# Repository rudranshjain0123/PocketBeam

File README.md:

# PocketBeam

A flashlight right?
Is a flashlight, but a different one. 3 leds, a buzzer and even a darkness detector!

Exactly what we need for those nights when the power cuts.

A MANUAL CONTROL for when u need to have fun.
Powered by 2 aa, this packs a punch.
This is custom made by me in kicad.
# Whats INSIDE
It includes resistors, a capacitator, a detector, switches etc.
### IMG

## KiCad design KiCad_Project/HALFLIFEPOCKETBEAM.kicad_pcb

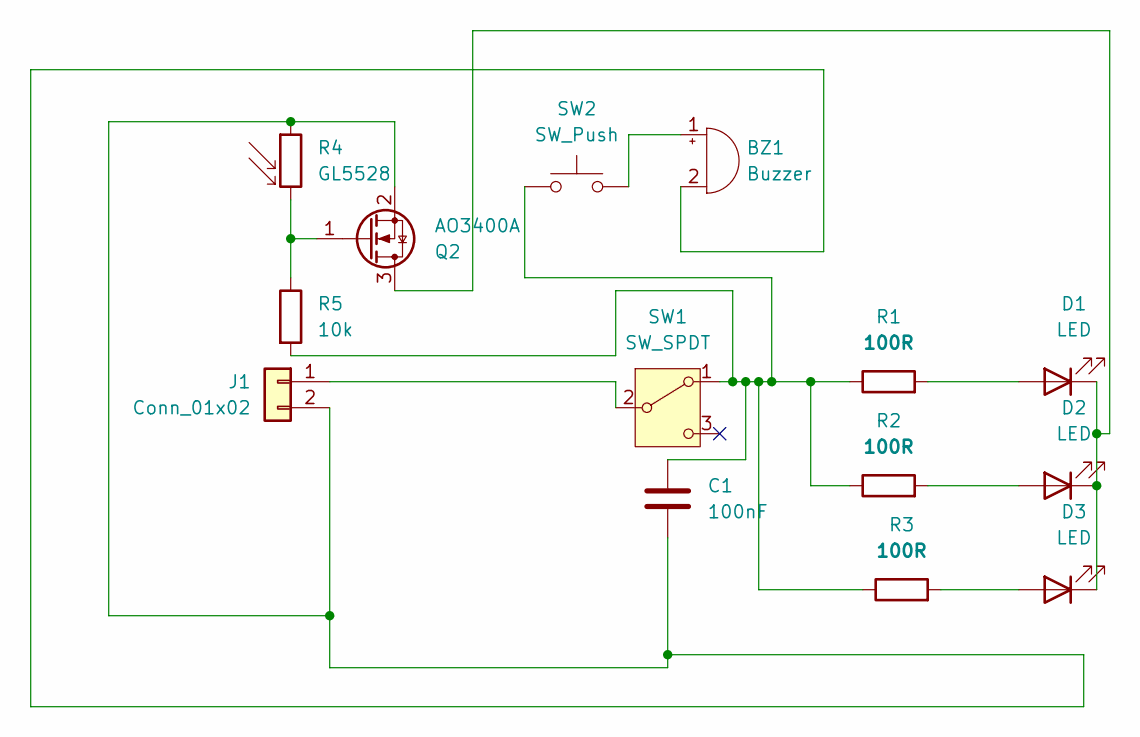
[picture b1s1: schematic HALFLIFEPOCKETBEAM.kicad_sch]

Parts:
BZ1: Buzzer; Buzzer_12x9.5RM7.6
C1: 100nF; C_Disc_D5.0mm_W2.5mm_P5.00mm
D1, D2, D3: LED; LED_D5.0mm_Horizontal_O1.27mm_Z15.0mm
J1: Conn_01x02; PinHeader_1x02_P2.54mm_Vertical
Q2: AO3400A; SOT-23
R1, R2, R3: 100R; R_Axial_DIN0207_L6.3mm_D2.5mm_P10.16mm_Horizontal
R4: GL5528; R_LDR_5.0x4.1mm_P3mm_Vertical
R5: 10k; R_Axial_DIN0207_L6.3mm_D2.5mm_P10.16mm_Horizontal
SW1: SW_SPDT; SW_Slide_SPDT_Straight_CK_OS102011MS2Q
SW2: SW_Push; SW_PUSH_6mm_H13mm

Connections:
unnamed: BZ1.1 (+), SW2.2
unnamed: BZ1.2 (-), C1.2, J1.2, Q2.2 (S), R4.1
unnamed: D1.2 (A), R1.2
unnamed: D1.1 (K), D2.1 (K), D3.1 (K), Q2.3 (D)
unnamed: D2.2 (A), R2.2
unnamed: D3.2 (A), R3.2
unnamed: J1.1, SW1.2 (B)
unnamed: Q2.1 (G), R4.2, R5.1
unnamed: C1.1, R1.1, R2.1, R3.1, R5.2, SW1.1 (A), SW2.1

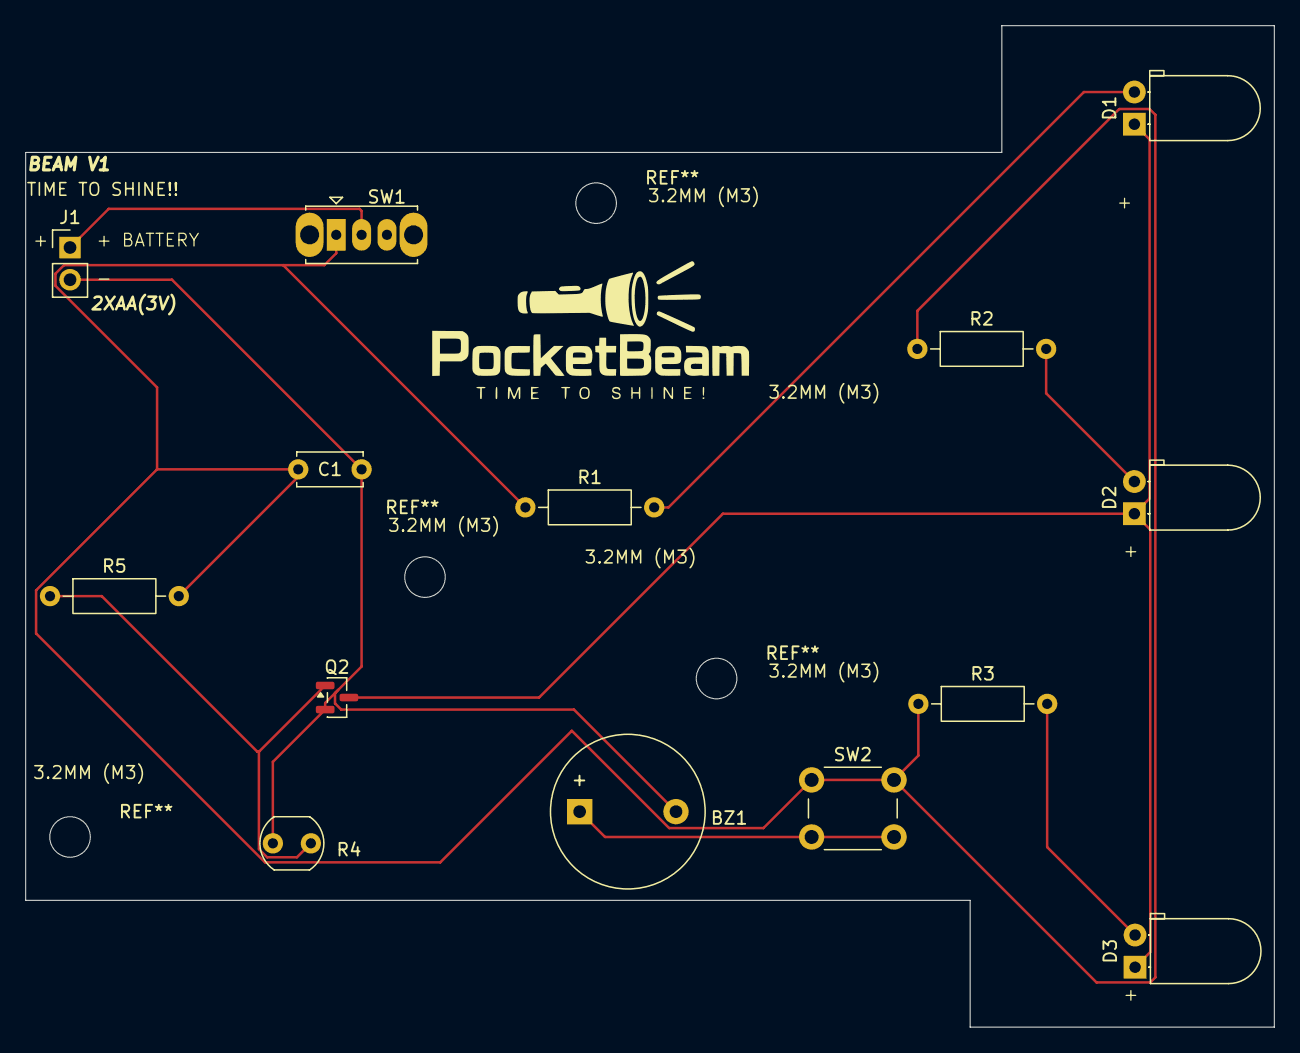
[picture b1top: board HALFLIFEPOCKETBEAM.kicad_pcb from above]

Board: 2 copper layers, 98.5 x 79.0 mm, 14 parts (0 on the bottom side), 9 nets.

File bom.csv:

"Reference","Qty","Value","DNP","Exclude from BOM","Exclude from Board","Exclude from Simulation","Exclude from Position Files","Footprint","Datasheet"
"BZ1","1","Buzzer","","","","","${EXCLUDE_FROM_POS_FILES}","Buzzer_Beeper:Buzzer_12x9.5RM7.6",""
"C1","1","100nF","","","","","${EXCLUDE_FROM_POS_FILES}","Capacitor_THT:C_Disc_D5.0mm_W2.5mm_P5.00mm",""
"D1,D2,D3","3","LED","","","","","${EXCLUDE_FROM_POS_FILES}","LED_THT:LED_D5.0mm_Horizontal_O1.27mm_Z15.0mm",""
"J1","1","Conn_01x02","","","","","${EXCLUDE_FROM_POS_FILES}","Connector_PinHeader_2.54mm:PinHeader_1x02_P2.54mm_Vertical",""
"Q2","1","AO3400A","","","","","${EXCLUDE_FROM_POS_FILES}","Package_TO_SOT_SMD:SOT-23",""
"R1,R2,R3","3","100R","","","","","${EXCLUDE_FROM_POS_FILES}","Resistor_THT:R_Axial_DIN0207_L6.3mm_D2.5mm_P10.16mm_Horizontal",""
"R4","1","GL5528","","","","","${EXCLUDE_FROM_POS_FILES}","OptoDevice:R_LDR_5.0x4.1mm_P3mm_Vertical","http://www.elektronica-componenten.nl/WebRoot/StoreNL/Shops/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"
"R5","1","10k","","","","","${EXCLUDE_FROM_POS_FILES}","Resistor_THT:R_Axial_DIN0207_L6.3mm_D2.5mm_P10.16mm_Horizontal",""
"SW1","1","SW_SPDT","","","","","${EXCLUDE_FROM_POS_FILES}","Button_Switch_THT:SW_Slide_SPDT_Straight_CK_OS102011MS2Q",""
"SW2","1","SW_Push","","","","","${EXCLUDE_FROM_POS_FILES}","Button_Switch_THT:SW_PUSH_6mm_H13mm",""
